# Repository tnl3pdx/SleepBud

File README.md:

## ECE 411 Team 3 - SleepBud
## Members
- Ameer Melli
- Cristian Gomez
- Paul Nguyen
- Truong Le

## Product Overview
Sleep Bud transcends the functionality of a simple alarm clock, serving as a comprehensive sleep companion designed to enhance your sleep quality. It features mood-inducing lights and gentle non-intrusive waking sounds. Essentially, this innovative device is a hybrid between a traditional alarm clock and a multi-color lamp.
Why?? Because according to the CDC 70 million Americans have chronic sleep problems and the current market solutions are too expensive. 

## User Manual for SleepBud

Mode 0: (normal mode indicated by teal colored colon)
- This will be where the clock will display the appropriate time.
- (mode button) Button 0 pressed in mode 0 will change the mode.
- (plus button) Button 1 pressed in mode 0 will increase the brightness of the lamp.
- (minus button) Button 2 pressed in mode 0 will decrease the brightness of the lamp.
- (select button) Button 3 pressed in mode 0 will cycle through lamp colors.

- In mode 0, when the alarm is set the bottom colon will be purple indicating the alarm is set.
- In mode 0, when the alarm is set, button 3 (the select button) acts as a snooze button.

- In mode 0, when in AM time (00:00 - 12:00) the digits will be a warm color (orange).
- In mode 0, when in PM time (12:00 - 24:00) the digits will be a cool color (white).

- In mode 0, when waving your hand over the alarm, the PIR sensor will automatically turn off the lamp if it is on and if it is off, it will turn it on.

Mode 1: (configuration time mode indicated by red colored colon)
- This will be where the user can manually set the clock time.
- (mode button) Button 0 pressed in mode 1 will cycle to the next mode and set the new time.
- (plus button) Button 1 pressed in mode 1 will increase the value of the selected section for the manual time.
- (minus button) Button 2 pressed in mode 1 will decrease the value of the selected section for the manual time.
- (select button) Button 3 pressed in mode 1 will cycle through the digits.

Mode 2: (enable alarm mode indicated by green colored colon)
- This will be for toggling the alarm on and off.
- (mode button) Button 0 pressed in mode 2 will cycle to the next mode and set the alarm.
- (plus button) Button 1 pressed in mode 2 will toggle on (1).
- (minus button) Button 2 pressed in mode 2 will toggle off (0).

Mode 3: (configuration alarm mode indicated by purple colored colon)
- This is for setting the alarm time.
- (mode button) Button 0 pressed in mode 3 will cycle to the next mode and set the new alarm time.
- (plus button) Button 1 pressed in mode 3 will increase the value of the selected section for the alarm time.
- (minus button) Button 2 pressed in mode 3 will decrease the value of the selected section for the alarm time.
- (select button) Button 3 pressed in mode 3 will cycle through the digits colors.

Mode 4: (select UTC mode indicated by yellow colored colon)
- This sets the UTC offset.
- (mode button) Button 0 pressed in mode 4 will cycle to the next mode and set the new UTC offset.
- (plus button) Button 1 pressed in mode 4 will increase the value of the selected section for the UTC offset.
- (minus button) Button 2 pressed in mode 4 will decrease the value of the selected section for the UTC offset.

- In mode 4, when indicating what UTC offset you want when adding a positive offset the digits will be green.
- In mode 4, when indicating what UTC offset you want when adding a negative offset the digits will be red.

Mode 5: (enable NTP update mode indicated by pink colored colon)
- This enables time fetch from wifi and applies UTC offset.
- (mode button) Button 0 pressed in mode 5 will cycle to the next mode and set enable NTP.
- (plus button) Button 1 pressed in mode 5 will toggle on (1).
- (minus button) Button 2 pressed in mode 5 will toggle off (0).

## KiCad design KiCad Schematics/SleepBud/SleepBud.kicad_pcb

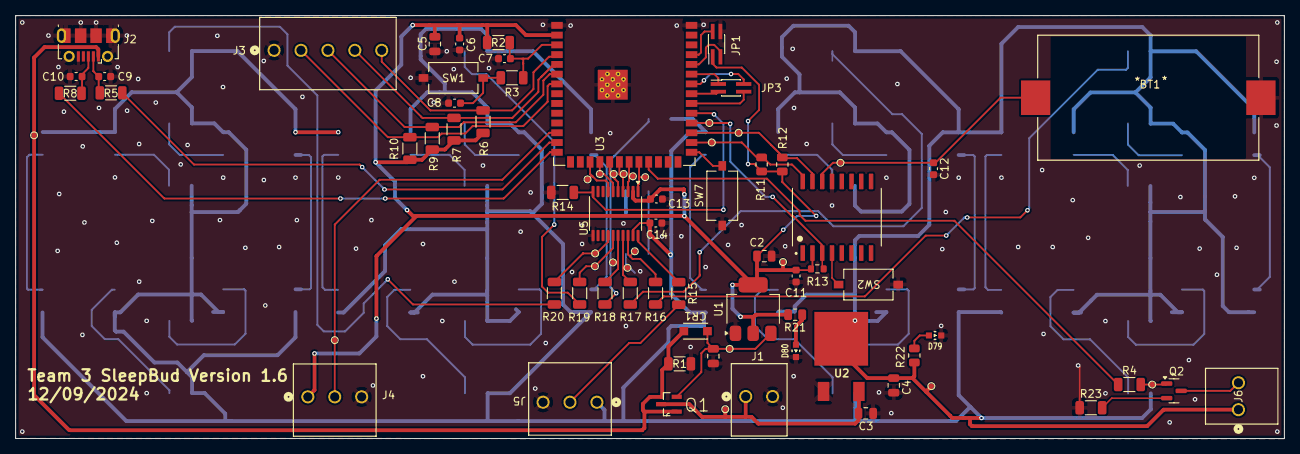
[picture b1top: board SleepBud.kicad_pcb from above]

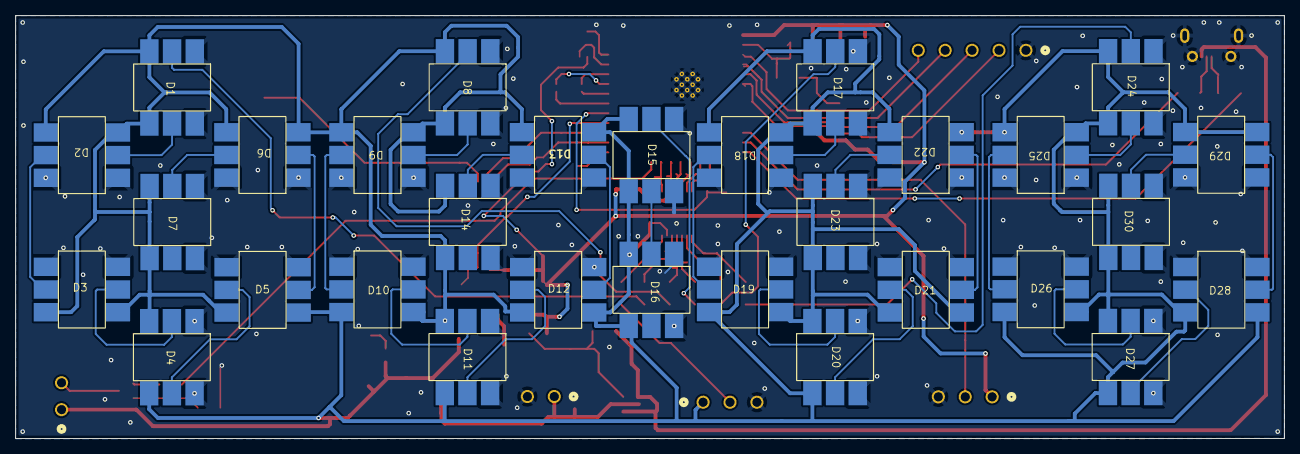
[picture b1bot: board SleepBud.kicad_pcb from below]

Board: 2 copper layers, 165.0 x 55.0 mm, 111 parts (30 on the bottom side), 79 nets.

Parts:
BT1: Battery_Cell_3V; BH-74G-5-P_ADM
C1, C3: 10uF; C_0805_2012Metric
C2, C4, C5: 22uF; C_0805_2012Metric
C6, C8, C11, C12, C13, C14: 0.1uF; C_0603_1608Metric
C7: 1uF; C_0603_1608Metric
C9, C10: 22pF; C_0603_1608Metric
CR1: MBR120LSFT3G; SDO_SOD-123FL498_OSI
D1, D2, D3, D4, D5, D6, D7, D8, D9, D10, D11, D12, D13, D14, D15, D16, D17, D18, D19, D20, D21, D22, D23, D24, D25, D26, D27, D28, D29, D30: WS2812B; WB2812B
D79, D80: WL-SMCW_0603
J1: 12V Barrel Jack; CONN_1984769_PXC
J2: USB_B_Micro; USB_Micro-B_Molex-105017-0001
J3: Button Connector; CONN_1984798_PXC
J4: AM312 Connector; CONN_1984772_PXC
J5: LED Lamp Connector; CONN_1984772_PXC
J6: Connector to Buzzer; CONN_1984769_PXC
JP1: UART; PinHeader_2x02_P1.00mm_Vertical_SMD
JP3: JTAG; PinHeader_2x02_P1.00mm_Vertical_SMD
Q1: DMG3415U-7; SOT95P240X105-3N
Q2: AO3400A; SOT-23
R1, R2, R6, R7, R9, R10, R23: 10k; R_1206_3216Metric
R3, R5, R8: 0; R_1206_3216Metric
R4, R15, R16, R17, R18, R19, R20: 470; R_1206_3216Metric
R11, R12: 3.3k; R_0805_2012Metric
R13: 4.7k; R_0603_1608Metric
R14: 10kOhm; R_1206_3216Metric
R21: 100; R_0805_2012Metric
R22: 180; R_0805_2012Metric
SW1: EN Button; SW_Tactile_SPST_NO_Straight_CK_PTS636Sx25SMTRLFS
SW2: Reset Button; SW_Tactile_SPST_NO_Straight_CK_PTS636Sx25SMTRLFS
SW7: Boot Button; SW_Tactile_SPST_NO_Straight_CK_PTS636Sx25SMTRLFS
TP1, TP2, TP3, TP4, TP5, TP6, TP7, TP8, TP9, TP10, TP11, TP12, TP13, TP14, TP15, TP22: TestPoint_Flag; Testpoint Pad
TP16, TP17, TP18, TP19, TP20, TP21: TestPoint_Small; Testpoint Pad
U1: AMS1117-3.3; SOT-223-3_TabPin2
U2: AZ1084CD
U3: ESP32-S3-WROOM-1
U4: DS3231SN_; SOIC127P1032X265-16N
U5: TXS0108EPW; TSSOP-20_4.4x6.5mm_P0.65mm

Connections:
+3.3V: C2.1, C5.1, C6.1, C11.1, C13.1, J4.1, JP1.1 (VCC), R2.1, R6.1, R7.1, R9.1, R10.1, R11.1, R12.1, R13.1, R21.2, TP8.1, U1.2 (VO), U3.2 (3V3), U4.2 (VCC), U5.2 (VCCA)
+5V: C4.1, C14.1, D1.1 (VDD), D2.1 (VDD), D3.1 (VDD), D4.1 (VDD), D5.1 (VDD), D6.1 (VDD), D7.1 (VDD), D8.1 (VDD), D9.1 (VDD), D10.1 (VDD), D11.1 (VDD), D12.1 (VDD), D13.1 (VDD), D14.1 (VDD), D15.1 (VDD), D16.1 (VDD), D17.1 (VDD), D18.1 (VDD), D19.1 (VDD), D20.1 (VDD), D21.1 (VDD), D22.1 (VDD), D23.1 (VDD), D24.1 (VDD), D25.1 (VDD), D26.1 (VDD), D27.1 (VDD), D28.1 (VDD), D29.1 (VDD), D30.1 (VDD), J5.1, J6.1, R22.2, TP7.1, U2.2 (VO), U5.19 (VCCB)
+12V: C3.1, J1.1, Q1.3 (D), TP6.1, U2.3 (VI)
/B2 - Digit 1: R16.1, TP5.1, U5.18 (B2)
/B3 - Digit 2: R17.1, TP4.1, U5.17 (B3)
/B4 - Colon: R18.1, TP3.1, U5.16 (B4)
/B5 - Digit 3: R19.1, TP2.1, U5.15 (B5)
/B6 - Digit 4: R20.1, TP1.1, U5.14 (B6)
/Buzzer: R4.1, U3.23 (IO21)
/IO8 - Output2: J4.2, TP11.1, U3.12 (IO8)
/IO9 - A6: TP21.1, U3.17 (IO9), U5.7 (A6)
/IO10 - A5: TP20.1, U3.18 (IO10), U5.6 (A5)
/IO11 - A4: TP19.1, U3.19 (IO11), U5.5 (A4)
/IO12 - A3: TP18.1, U3.20 (IO12), U5.4 (A3)
/IO13 - A2: TP17.1, U3.21 (IO13), U5.3 (A2)
/IO14 - A1: TP16.1, U3.22 (IO14), U5.1 (A1)
/IO35-SCL: R11.2, TP13.1, U3.28 (IO35), U4.16 (SCL)
/IO36-SDA: R12.2, TP14.1, U3.29 (IO36), U4.15 (SDA)
/IO37-SQW/INT: R13.2, TP15.1, U3.30 (IO37), U4.3 (SQW/~INT)
/IO38-OE: R14.1, U3.31 (IO38), U5.10 (OE)
GND: BT1.2 (-), C1.2, C2.2, C3.2, C4.2, C5.2, C6.2, C7.1, C8.1, C9.2, C10.2, C11.2, C12.2, C13.2, C14.2, D1.3 (VSS), D2.3 (VSS), D3.3 (VSS), D4.3 (VSS), D5.3 (VSS), D6.3 (VSS), D7.3 (VSS), D8.3 (VSS), D9.3 (VSS), D10.3 (VSS), D11.3 (VSS), D12.3 (VSS), D13.3 (VSS), D14.3 (VSS), D15.3 (VSS), D16.3 (VSS), D17.3 (VSS), D18.3 (VSS), D19.3 (VSS), D20.3 (VSS), D21.3 (VSS), D22.3 (VSS), D23.3 (VSS), D24.3 (VSS), D25.3 (VSS), D26.3 (VSS), D27.3 (VSS), D28.3 (VSS), D29.3 (VSS), D30.3 (VSS), D79.1, D80.1, J1.2, J2.5 (GND), J2.6 (Shield), J3.1, J4.3, J5.3, JP1.4 (GND), R1.2, R14.2, R23.1, SW1.1, SW2.1, SW7.1, U1.1 (GND), U2.1 (GND), U3.1 (GND), U3.40 (GND), U3.41 (GND), U4.13 (GND), U5.11 (GND)
unnamed: BT1.1 (+), C12.1, TP22.1, U4.14 (VBAT)
unnamed: C8.2, R3.1, SW1.2
unnamed: D1.4 (DIN), R16.2
unnamed: D1.2 (DOUT), D2.4 (DIN)
unnamed: D2.2 (DOUT), D3.4 (DIN)
unnamed: D3.2 (DOUT), D4.4 (DIN)
unnamed: D4.2 (DOUT), D5.4 (DIN)
unnamed: D5.2 (DOUT), D6.4 (DIN)
unnamed: D6.2 (DOUT), D7.4 (DIN)
unnamed: D8.4 (DIN), R17.2
unnamed: D8.2 (DOUT), D9.4 (DIN)
unnamed: D9.2 (DOUT), D10.4 (DIN)
unnamed: D10.2 (DOUT), D11.4 (DIN)
unnamed: D11.2 (DOUT), D12.4 (DIN)
unnamed: D12.2 (DOUT), D13.4 (DIN)
unnamed: D13.2 (DOUT), D14.4 (DIN)
unnamed: D15.4 (DIN), R18.2
unnamed: D15.2 (DOUT), D16.4 (DIN)
unnamed: D17.4 (DIN), R19.2
unnamed: D17.2 (DOUT), D18.4 (DIN)
unnamed: D18.2 (DOUT), D19.4 (DIN)
unnamed: D19.2 (DOUT), D20.4 (DIN)
unnamed: D20.2 (DOUT), D21.4 (DIN)
unnamed: D21.2 (DOUT), D22.4 (DIN)
unnamed: D22.2 (DOUT), D23.4 (DIN)
unnamed: D24.4 (DIN), R20.2
unnamed: D24.2 (DOUT), D25.4 (DIN)
unnamed: D25.2 (DOUT), D26.4 (DIN)
unnamed: D26.2 (DOUT), D27.4 (DIN)
unnamed: D27.2 (DOUT), D28.4 (DIN)
unnamed: D28.2 (DOUT), D29.4 (DIN)
unnamed: D29.2 (DOUT), D30.4 (DIN)
unnamed: D79.2, R22.1
unnamed: D80.2, R21.1
unnamed: C10.1, J2.3 (D+), R8.2
unnamed: C9.1, J2.2 (D-), R5.2
unnamed: J5.2, R15.2
unnamed: JP1.3 (RXD0), U3.36 (RXD0)
unnamed: JP1.2 (TXD0), U3.37 (TXD0)
unnamed: JP3.4 (TCK), U3.32 (IO39)
unnamed: JP3.2 (TDI), U3.34 (IO41)
unnamed: JP3.3 (TDO), U3.33 (IO40)
unnamed: JP3.1 (TMS), U3.35 (IO42)
unnamed: C1.1, CR1.1, Q1.2 (S), TP9.1, U1.3 (VI)
unnamed: J6.2, Q2.3 (D)
unnamed: Q2.1 (G), R4.2, TP12.1
unnamed: Q2.2 (S), R23.2
unnamed: C7.2, R2.2, R3.2, U3.3 (EN)
unnamed: SW7.2, U3.27 (IO0)
unnamed: J3.5, R6.2, U3.4 (IO4)
unnamed: J3.4, R7.2, U3.5 (IO5)
unnamed: J3.3, R9.2, U3.6 (IO6)
unnamed: J3.2, R10.2, U3.7 (IO7)
unnamed: R5.1, U3.13 (IO19)
unnamed: R8.1, U3.14 (IO20)
unnamed: SW2.2, U4.4 (~RST)
unnamed: R15.1, U5.20 (B1)
VBUS: CR1.2, J2.1 (VBUS), Q1.1 (G), R1.1, TP10.1

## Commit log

2024-10-24 Work Log Update
    - Create LED Display Testbench
2024-10-24 Initialize KiCad
    Couple Schematics In to Test
2024-10-24 New SleepBud Folder Directory
    sup
2024-10-26 Version 10/25
    Added connections
2024-10-26 new version with updated stuff
2024-11-01 Create initial test code for RTC
    - Tested RTC lib
    - Configured time and alarm time
    - Simple polling function to read RTC clock
2024-11-02 SleepBud Schematic 11/1/2024
2024-11-02 This is the PIR test code
    This uses the PIR that waits for motion and then indicates if motion has been detected or motion stopped being detected.
2024-11-02 WiFi Implementation with RTC
    - Added WiFi to fetch time data using NTP library
    - Added parser function for breaking down NTP string data
    - Integrated parser with time set function for RTC
2024-11-02 Test code for passive buzzer
    This generates 90+ dB for the buzzer with delays and changing tones. There is also code for an active buzzer if we like that better.
2024-11-06 Create Test Program for LEDs
    - Created test program for lighting up LEDs
    - Created wrapper function to display number based on preset array
2024-11-06 Version 1.1
2024-11-06 Finished Wiring Schematic
    Wiring is finished, however there are 10 errors left that need to be checked/ fixed
2024-11-06 MultiLED Array Support
    - Can now interface with multiple instances of LED arrays with single function
    - Can set color of a set of arrays
    - Digit arrays are handled based on input number
2024-11-06 Added Footprints to most things
2024-11-07 Initial Program Setup
    - Transferred pre-processor directives, objects, and variables from test programs to main
    - Created config.h to hold pin assignments and LED array lengths
2024-11-07 Finish Most Footprint, Started Layout
2024-11-07 Moving PIR
    Moving PIR to correct folder.
2024-11-08 Moving Buzzer Folder
    This moves the buzzer code to the correct folder
2024-11-08 Revert "Moving Buzzer Folder"
    This reverts commit 946b4f6aadbfe2fb92f8ac278ed7cf92d526357d.
2024-11-08 Buzzer Folder without DS
    This moves the buzzer into the correct folder.
2024-11-08 DS store ignore
    For mac users ignores the DS file that is added
2024-11-08 For Switch (needs to cut)
    This is just a starting box for how the kill switch can be held.
2024-11-08 Switched some footprints and schematics
2024-11-08 Add WS2128B Custom Pad Layout Reference
2024-11-08 Updated Footprints
    Footprint for WB2812B LED was personalized
2024-11-09 Create Setup Functions
    - Created genSetup to setup all objects needed for clock
    - Created wifiNTP to connect to WIfI to update time
    - Created rtcSet to set current time on RTC module
    - Added LED functions from LEDTest program
2024-11-09 Bug FIxes
    - Added WiFi cred variables that were forgotten
    - Added valid checks for begin functions
    - Added configInit key to Preferences to check if namespace has been allocated
2024-11-09 Adding Clock Digits (unsized)
    This was based on a reference found online and needs to be sized down for our needs (optional needs diffuser white prints to cover each digit side)
2024-11-10 just moved some stuff around and changed some texts
2024-11-11 Updated the Custom Pad
    Moved to the right place
2024-11-11 Placed Parts to Potential area on Layout
2024-11-12 Back of PCB Almost Done, Started on Front
2024-11-14 PCB Work on V1.1
2024-11-14 Pads
    Pads for 12V-5V chip
2024-11-14 AZ1084CD pad
    12V-5V pad
2024-11-14 PCB Layout Routing Rough Draft Finished
2024-11-14 change title for layput
2024-11-15 Fixed all violations on PCB
    Just need to work on grounding parts, and switching mosfets, adding connections
2024-11-16 PCB Done Needs Checking Over
    All NECESSARY warnings/errors are resolved just need checking with entire team/design review by others
2024-11-16 Added LED Set Helper Functions
    - Added setDigitLED function to set HSV per digit on display
    - Added timeDisplay as wrapper for setDigitLED
    - Created setAuxLED as helper for setting up aux LEDs (mode LEDs, lamp LEDs
2024-11-16 Bug Fixes
    - Fixed narrowing warning due to incorrect casting to uint8_t
    - Added disconnect code for WiFi
2024-11-18 Changed PMosfet
    Change the Mosfet can be seen on schematic and PCB layout
2024-11-18 Added Some Ground Vias to each Corner of the Board
    Still missing the ground stitching for some components, will work on it it later
2024-11-19 Added Some More Ground Vias
    I think I did the ground stitching correctly, need team to check if its correct.
2024-11-19 Bug Fixes
    - Added debug code to check for successful NTP packet fetch
2024-11-20 This is the button interupt code
2024-11-20 Kill switch V2
    This is just the sized version for the kill switch to slide into.
2024-11-20 Finished PCB V1.5
    Added LEDs to see if PCB is getting power
    Changed TestPoint sizes
    Added more grounds to even out board
2024-11-20 Added more grounds vias based off video
    also created new gerber files
2024-11-24 Final PCB
2024-12-01 Minor Fixes
    - S3 required I2C pins be declared
    - OE for logic shifter now has a pin t control data out to LEDs
2024-12-01 PIR Control
    - Added PIR Enable/Disable LED code
    - Can use PIR to turn on/off LEDs using interrupt
2024-12-03 Mode Test created
    This tests the logic of the interrupts for the mode and the buttons.
2024-12-04 Implemented general layout for menu navigation
    -Reorganized loop to select certain functions depending on the mode selected
2024-12-04 This is untested Mode interrupts integration
    This still needs mode 4 to be added. Also is untested
2024-12-05 changed schematic from 12v/3a to 7v 3a
2024-12-05 wrote 7v instead of 9v on schematic
2024-12-05 Updated for case 4 set time manually
    This is the updated test case
2024-12-05 chnaged power supply once more
2024-12-05 Add Testing Program
2024-12-05 Updated sleepbud for modes (untested)
    This adds case 4 to the sleep bud main
2024-12-05 Added Button Defines and Organized Functions
2024-12-05 Moved some stuff around to make it look pretty
2024-12-05 Reorganized code to prep for merge
    - Removing some unneeded code from prior testing
2024-12-05 Adding UTC offset data
    This adds multi array for UTC offset
2024-12-05 Add buttons to config and remove from main
2024-12-06 Slightly fixed
2024-12-07 Reconfigured LED and Buzzer Setup
    - Fixed RTC call (update changed function)
    - Added Buzzer Pin config
    - Add Reversed LED array matrix data for flipped display
2024-12-10 1.6 Final version of both schematic and pcb
    This is the final version. Includes the change from 12V to 5V power supply, resistor values changed to the audio module and esthetical changes to the schematic including resizing of page and rewiring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
2024-12-10 Implemented Polling Functions for Buttons
    - Changed interrupts to polling for user UI
    - Reorganized variables from prior merges
2024-12-10 Tweaked Debounce for Buttons
2024-12-11 Added Test Function for Display
2024-12-12 Bug Fix for Test Function
2024-12-12 Update Color section for modes
2024-12-12 Fixing color table stuff
2024-12-12 Added Functions for Modes
    - Added user interface for normalLoop
    - Added user interface for enableNTPUpdate
2024-12-12 Adding seconds functions
2024-12-12 Added Features
    - PIR ISR is now implemented
    - Preference updates to NVS object now implemented for lamp brightness and utcOffset
2024-12-13 Code for mode 1 to set time manually
2024-12-13 Updated PIR to be Interrupt
2024-12-13 Final Functions
    - Final touches and debugging for all modes
    - Implemented utcOffset menu
    - Implemented enabling of alarm
    - Added configuration for alarm and time
2024-12-13 Added STL files for Case
2024-12-13 Added Blinking to Wifi Fetch and Fixed Colors
2024-12-14 Fixed Time Bug
2024-12-14 Fixed Time Keeping Bug
